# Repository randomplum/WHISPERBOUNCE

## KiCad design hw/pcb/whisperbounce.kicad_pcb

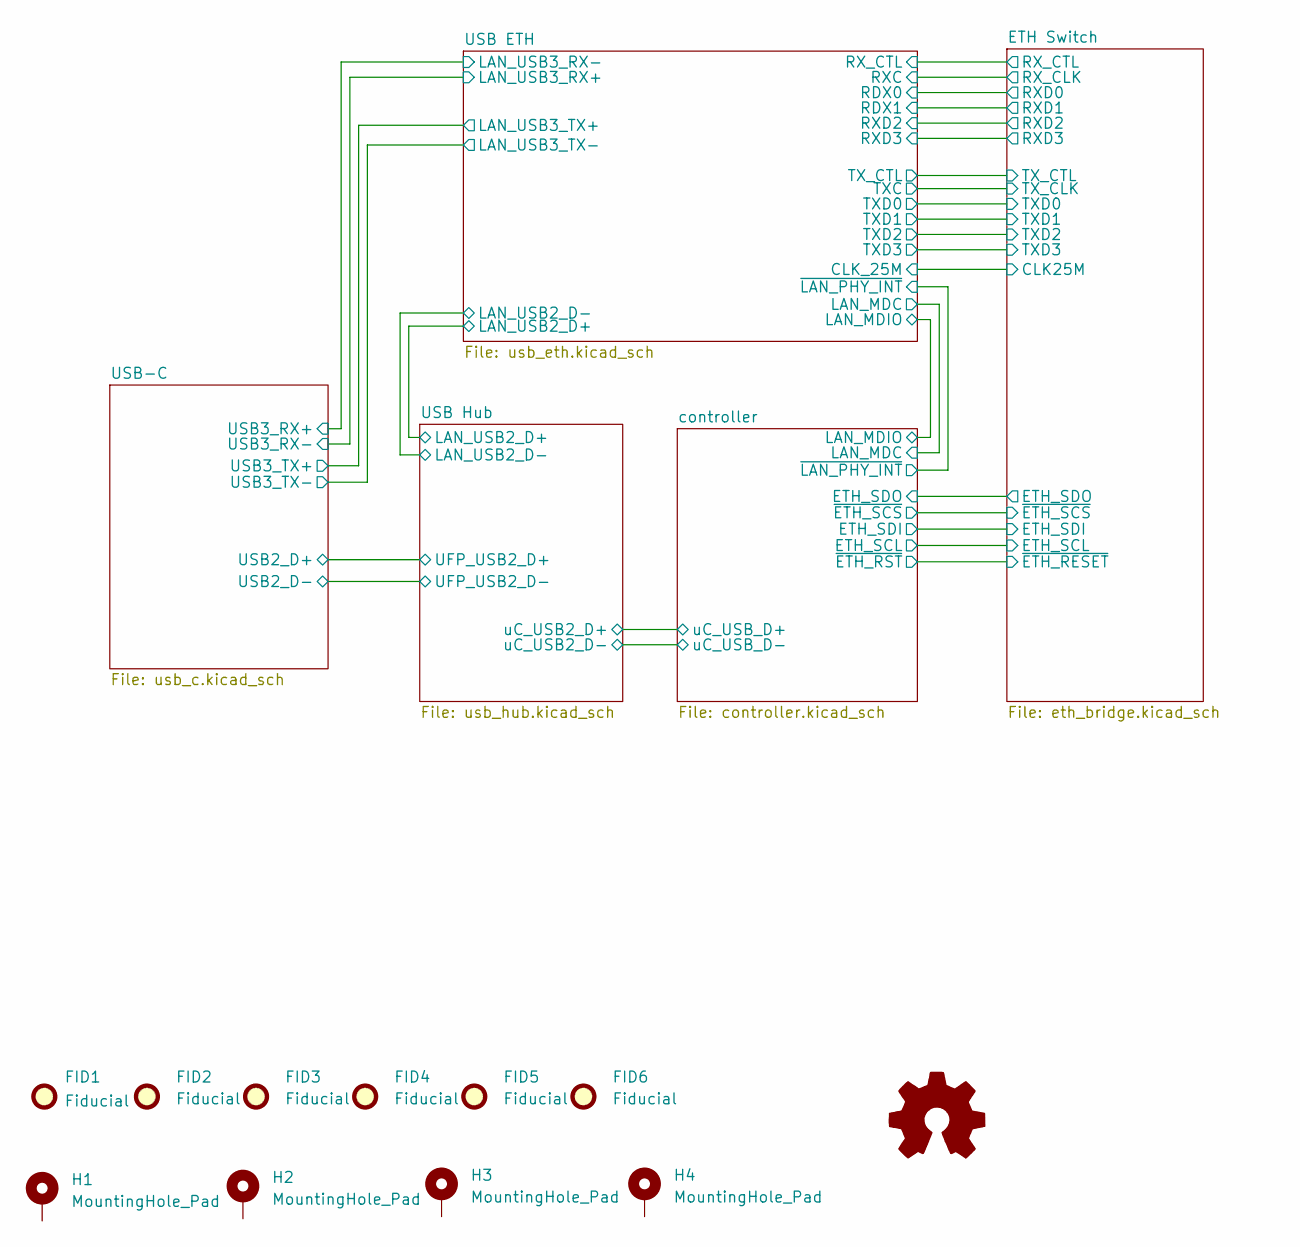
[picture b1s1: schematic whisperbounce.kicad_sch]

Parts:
FID1, FID2, FID3, FID4, FID5, FID6: Fiducial; Fiducial_0.75mm_Mask1.5mm
H1, H2, H3, H4: MountingHole_Pad; MountingHole_3.2mm_M3_Pad_Via

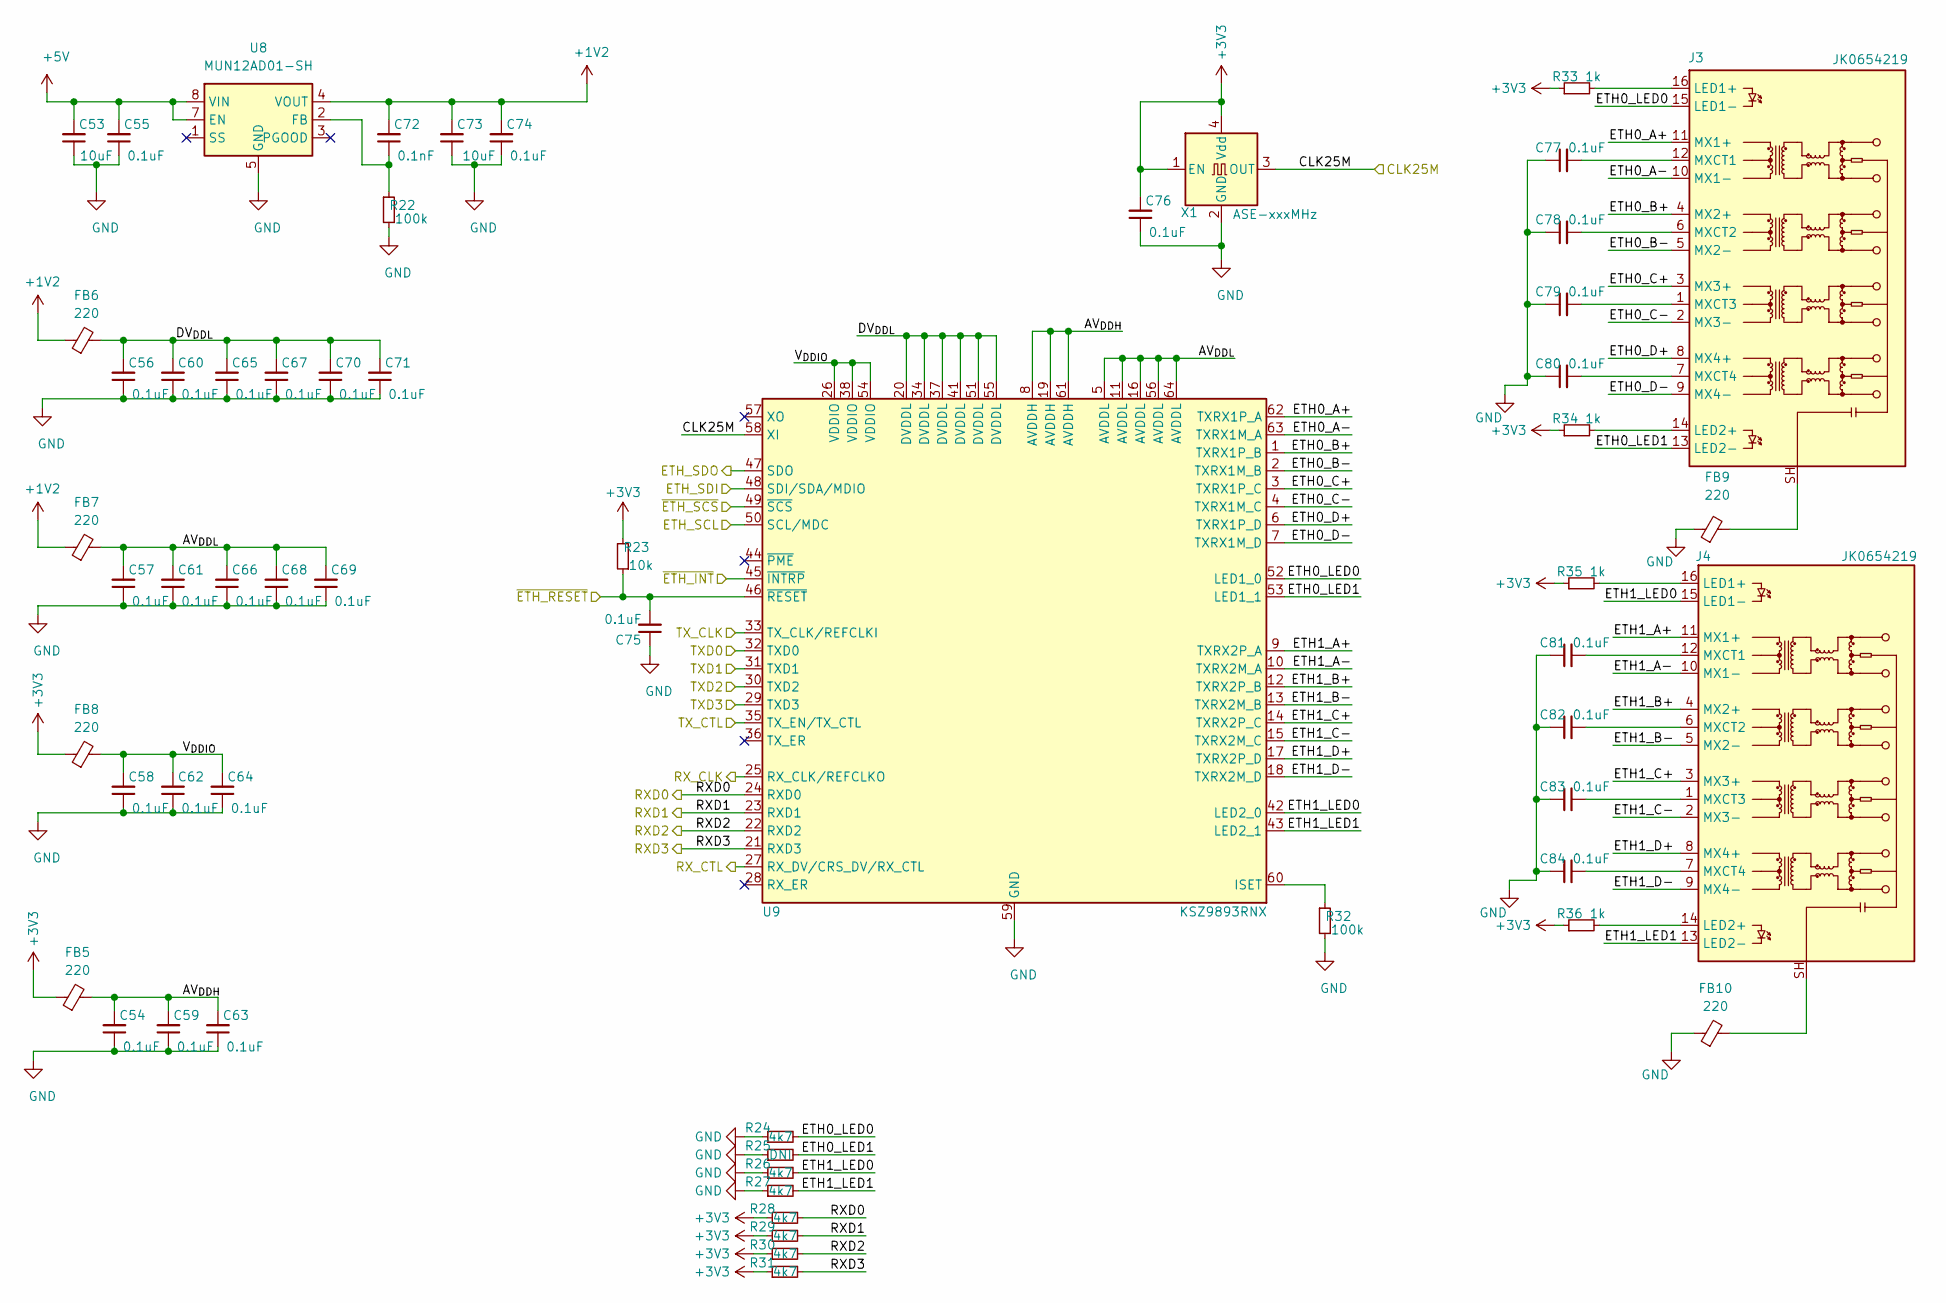
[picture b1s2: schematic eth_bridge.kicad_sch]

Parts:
C53, C73: 10uF; C_0402_1005Metric
C54, C55, C56, C57, C58, C59, C60, C61, C62, C63, C64, C65, C66, C67, C68, C69, C70, C71, C74, C75, C76, C77, C78, C79, C80, C81, C82, C83, C84: 0.1uF; C_0402_1005Metric
C72: 0.1nF; C_0402_1005Metric
FB5, FB6, FB7, FB8, FB9, FB10: 220; R_0603_1608Metric
J3, J4: JK0654219; RJ45_Pulse_JK0654219NL_Horizontal
R22, R32: 100k; R_0402_1005Metric
R23: 10k; R_0402_1005Metric
R24, R26, R27, R28, R29, R30, R31: 4k7; R_0402_1005Metric
R25: DNI; R_0402_1005Metric
R33, R34, R35, R36: 1k; R_0402_1005Metric
U8: MUN12AD01-SH; Converter_DCDC_Cyntec_MUN12AD01-SH
U9: KSZ9893RNX; QFN-64-1EP_8x8mm_P0.4mm_EP6.5x6.5mm_ThermalVias
X1: ASE-xxxMHz; Oscillator_SMD_Abracon_ASCO-4Pin_1.6x1.2mm

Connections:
+1V2: C72.2, C73.2, C74.2, FB6.1, FB7.1, U8.4 (VOUT)
+3V3: C76.2, FB5.1, FB8.1, R23.2, R28.1, R29.1, R30.1, R31.1, R33.1, R34.1, R35.1, R36.1, X1.1 (EN), X1.4 (Vdd); also elsewhere on the board
+5V: C53.2, C55.2, U8.7 (EN), U8.8 (VIN); also elsewhere on the board
/CLK_25M: U9.58 (XI), X1.3 (OUT); also elsewhere on the board
/ETH Switch/AV_{DDH}: C54.2, C59.2, C63.2, FB5.2, U9.8 (AVDDH), U9.19 (AVDDH), U9.61 (AVDDH)
/ETH Switch/AV_{DDL}: C57.2, C61.2, C66.2, C68.2, C69.2, FB7.2, U9.5 (AVDDL), U9.11 (AVDDL), U9.16 (AVDDL), U9.56 (AVDDL), U9.64 (AVDDL)
/ETH Switch/DV_{DDL}: C56.2, C60.2, C65.2, C67.2, C70.2, C71.2, FB6.2, U9.20 (DVDDL), U9.34 (DVDDL), U9.37 (DVDDL), U9.41 (DVDDL), U9.51 (DVDDL), U9.55 (DVDDL)
/ETH Switch/ETH0_A+: J3.11 (MX1+), U9.62 (TXRX1P_A)
/ETH Switch/ETH0_A-: J3.10 (MX1-), U9.63 (TXRX1M_A)
/ETH Switch/ETH0_B+: J3.4 (MX2+), U9.1 (TXRX1P_B)
/ETH Switch/ETH0_B-: J3.5 (MX2-), U9.2 (TXRX1M_B)
/ETH Switch/ETH0_C+: J3.3 (MX3+), U9.3 (TXRX1P_C)
/ETH Switch/ETH0_C-: J3.2 (MX3-), U9.4 (TXRX1M_C)
/ETH Switch/ETH0_D+: J3.8 (MX4+), U9.6 (TXRX1P_D)
/ETH Switch/ETH0_D-: J3.9 (MX4-), U9.7 (TXRX1M_D)
/ETH Switch/ETH0_LED0: J3.15 (LED1-), R24.2, U9.52 (LED1_0)
/ETH Switch/ETH0_LED1: J3.13 (LED2-), R25.2, U9.53 (LED1_1)
/ETH Switch/ETH1_A+: J4.11 (MX1+), U9.9 (TXRX2P_A)
/ETH Switch/ETH1_A-: J4.10 (MX1-), U9.10 (TXRX2M_A)
/ETH Switch/ETH1_B+: J4.4 (MX2+), U9.12 (TXRX2P_B)
/ETH Switch/ETH1_B-: J4.5 (MX2-), U9.13 (TXRX2M_B)
/ETH Switch/ETH1_C+: J4.3 (MX3+), U9.14 (TXRX2P_C)
/ETH Switch/ETH1_C-: J4.2 (MX3-), U9.15 (TXRX2M_C)
/ETH Switch/ETH1_D+: J4.8 (MX4+), U9.17 (TXRX2P_D)
/ETH Switch/ETH1_D-: J4.9 (MX4-), U9.18 (TXRX2M_D)
/ETH Switch/ETH1_LED0: J4.15 (LED1-), R26.2, U9.42 (LED2_0)
/ETH Switch/ETH1_LED1: J4.13 (LED2-), R27.2, U9.43 (LED2_1)
/ETH Switch/V_{DDIO}: C58.2, C62.2, C64.2, FB8.2, U9.26 (VDDIO), U9.38 (VDDIO), U9.54 (VDDIO)
/ETH_SCL: U9.50 (SCL/MDC); also elsewhere on the board
/ETH_SDI: U9.48 (SDI/SDA/MDIO); also elsewhere on the board
/ETH_SDO: U9.47 (SDO); also elsewhere on the board
/RXD0: R28.2, U9.24 (RXD0); also elsewhere on the board
/RXD1: R29.2, U9.23 (RXD1); also elsewhere on the board
/RXD2: R30.2, U9.22 (RXD2); also elsewhere on the board
/RXD3: R31.2, U9.21 (RXD3); also elsewhere on the board
/RX_CLK: U9.25 (RX_CLK/REFCLKO); also elsewhere on the board
/RX_CTL: U9.27 (RX_DV/CRS_DV/RX_CTL); also elsewhere on the board
/TXC: U9.33 (TX_CLK/REFCLKI); also elsewhere on the board
/TXD0: U9.32 (TXD0); also elsewhere on the board
/TXD1: U9.31 (TXD1); also elsewhere on the board
/TXD2: U9.30 (TXD2); also elsewhere on the board
/TXD3: U9.29 (TXD3); also elsewhere on the board
/TX_CTL: U9.35 (TX_EN/TX_CTL); also elsewhere on the board
/~ETH_RST: C75.2, R23.1, U9.46 (~RESET); also elsewhere on the board
/~ETH_SCS: U9.49 (~SCS); also elsewhere on the board
GND: C53.1, C54.1, C55.1, C56.1, C57.1, C58.1, C59.1, C60.1, C61.1, C62.1, C63.1, C64.1, C65.1, C66.1, C67.1, C68.1, C69.1, C70.1, C71.1, C73.1, C74.1, C75.1, C76.1, C77.1, C78.1, C79.1, C80.1, C81.1, C82.1, C83.1, C84.1, FB9.1, FB10.1, R22.2, R24.1, R25.1, R26.1, R27.1, R32.2, U8.5 (GND), U8.9 (GND), U9.59 (GND), U9.65 (GND), X1.2 (GND); also elsewhere on the board
unnamed: C72.1, R22.1, U8.2 (FB)
unnamed: C77.2, J3.12 (MXCT1)
unnamed: C78.2, J3.6 (MXCT2)
unnamed: C79.2, J3.1 (MXCT3)
unnamed: C80.2, J3.7 (MXCT4)
unnamed: C81.2, J4.12 (MXCT1)
unnamed: C82.2, J4.6 (MXCT2)
unnamed: C83.2, J4.1 (MXCT3)
unnamed: C84.2, J4.7 (MXCT4)
unnamed: FB9.2, J3.SH
unnamed: FB10.2, J4.SH
unnamed: J3.14 (LED2+), R34.2
unnamed: J3.16 (LED1+), R33.2
unnamed: J4.14 (LED2+), R36.2
unnamed: J4.16 (LED1+), R35.2
unnamed: R32.1, U9.60 (ISET)

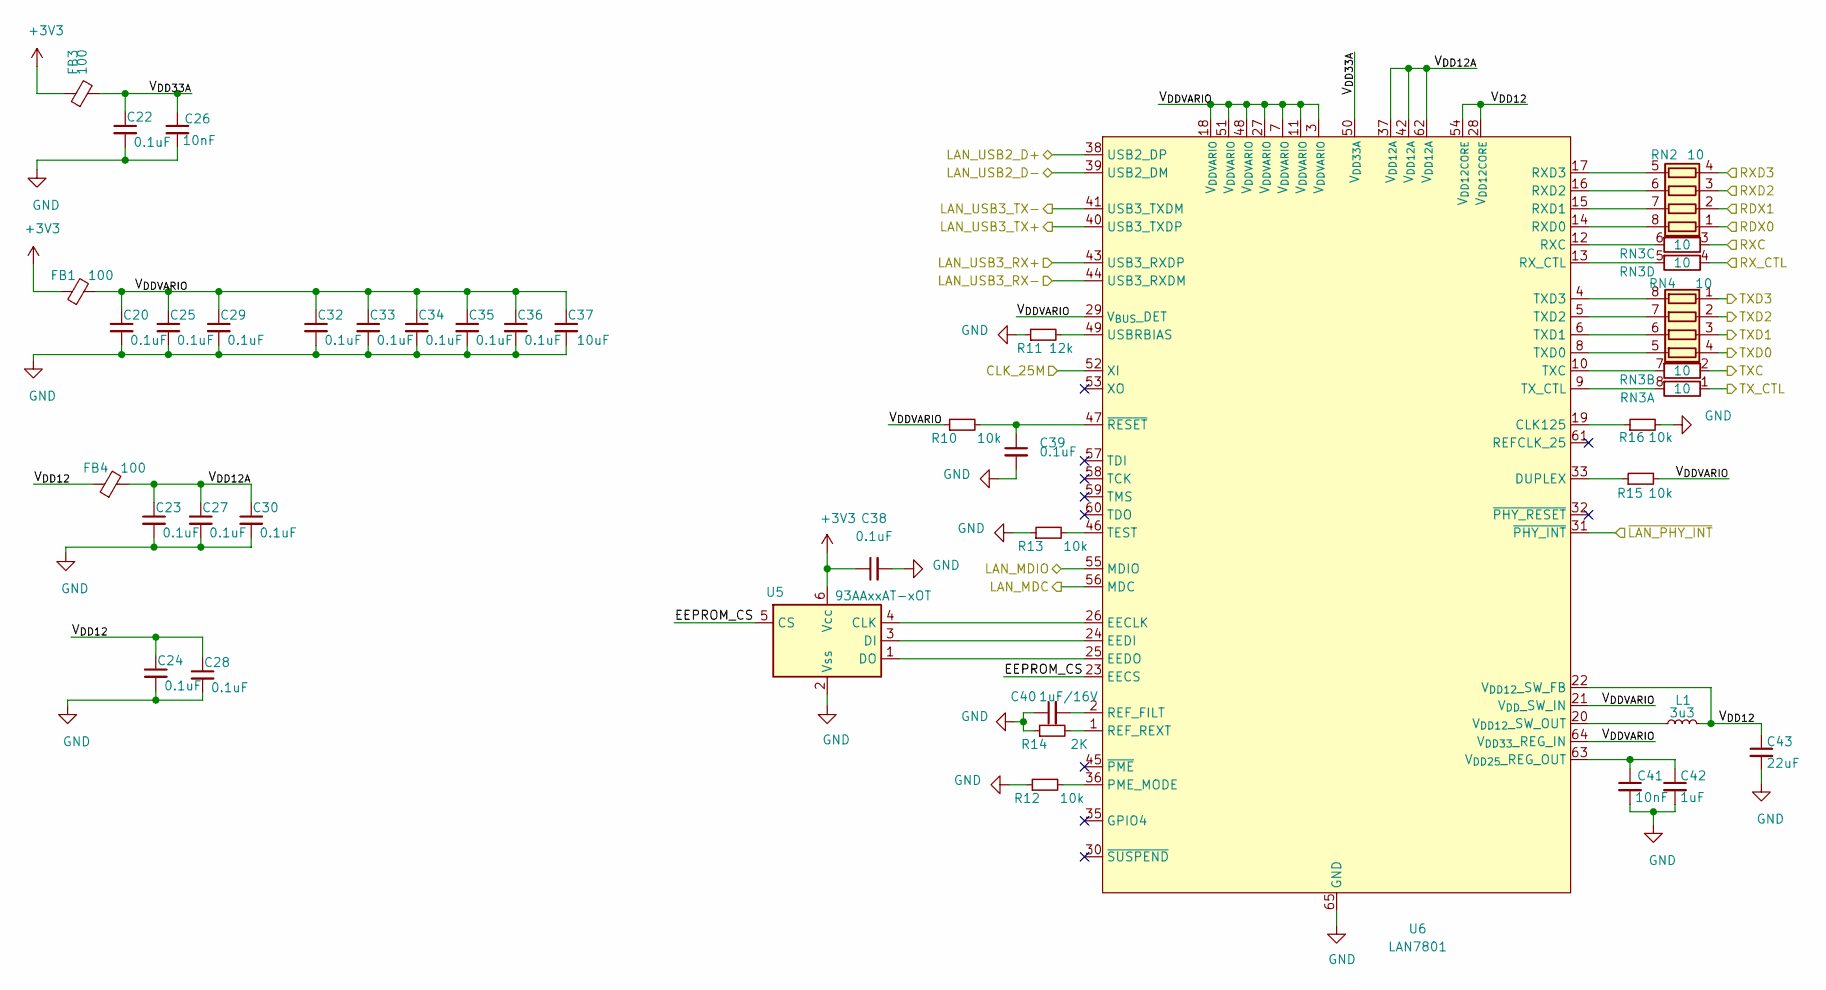
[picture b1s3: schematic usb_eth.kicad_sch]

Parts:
C20, C22, C23, C24, C25, C27, C28, C29, C30, C32, C33, C34, C35, C36, C38, C39: 0.1uF; C_0402_1005Metric
C26, C41: 10nF; C_0402_1005Metric
C37: 10uF; C_0402_1005Metric
C40: 1uF/16V; C_0402_1005Metric
C42: 1uF; C_0402_1005Metric
C43: 22uF; C_0805_2012Metric
FB1, FB3, FB4: 100; R_0603_1608Metric
L1: 3u3; L_Taiyo-Yuden_MD-2020
R10, R12, R13, R15, R16: 10k; R_0402_1005Metric
R11: 12k; R_0402_1005Metric
R14: 2K; R_0402_1005Metric
RN2, RN3, RN4: 10; R_Array_Convex_4x0402
U5: 93AAxxAT-xOT; SOT-23-6
U6: LAN7801; QFN-64-1EP_9x9mm_P0.5mm_EP6x6mm_ThermalVias

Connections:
+3V3: C38.1, FB1.1, FB3.1, U5.6 (Vсс); also elsewhere on the board
/CLK_25M: U6.52 (XI); also elsewhere on the board
/LAN_MDC: U6.56 (MDC); also elsewhere on the board
/LAN_MDIO: U6.55 (MDIO); also elsewhere on the board
/LAN_USB2_D+: U6.38 (USB2_DP); also elsewhere on the board
/LAN_USB2_D-: U6.39 (USB2_DM); also elsewhere on the board
/RXD0: RN2.1 (R1.1); also elsewhere on the board
/RXD1: RN2.2 (R2.1); also elsewhere on the board
/RXD2: RN2.3 (R3.1); also elsewhere on the board
/RXD3: RN2.4 (R4.1); also elsewhere on the board
/RX_CLK: RN3.3 (R3.1); also elsewhere on the board
/RX_CTL: RN3.4 (R4.1); also elsewhere on the board
/TXC: RN3.2 (R2.1); also elsewhere on the board
/TXD0: RN4.4 (R4.1); also elsewhere on the board
/TXD1: RN4.3 (R3.1); also elsewhere on the board
/TXD2: RN4.2 (R2.1); also elsewhere on the board
/TXD3: RN4.1 (R1.1); also elsewhere on the board
/TX_CTL: RN3.1 (R1.1); also elsewhere on the board
/USB3_RX+: U6.44 (USB3_RXDM); also elsewhere on the board
/USB3_RX-: U6.43 (USB3_RXDP); also elsewhere on the board
/USB3_TX+: U6.40 (USB3_TXDP); also elsewhere on the board
/USB3_TX-: U6.41 (USB3_TXDM); also elsewhere on the board
/USB ETH/EEPROM_CS: U5.5 (CS), U6.23 (EECS)
/USB ETH/V_{DD12A}: C23.1, C27.1, C30.1, FB4.2, U6.37 (V_{DD12A}), U6.42 (V_{DD12A}), U6.62 (V_{DD12A})
/USB ETH/V_{DD12}: C24.1, C28.1, C43.1, FB4.1, L1.2, U6.22 (V_{DD12}_SW_FB), U6.28 (V_{DD12CORE}), U6.54 (V_{DD12CORE})
/USB ETH/V_{DD33A}: C22.1, C26.1, FB3.2, U6.50 (V_{DD33A})
/USB ETH/V_{DDVARIO}: C20.1, C25.1, C29.1, C32.1, C33.1, C34.1, C35.1, C36.1, C37.1, FB1.2, R10.1, R15.2, U6.3 (V_{DDVARIO}), U6.7 (V_{DDVARIO}), U6.11 (V_{DDVARIO}), U6.18 (V_{DDVARIO}), U6.21 (V_{DD}_SW_IN), U6.27 (V_{DDVARIO}), U6.29 (V_{BUS}_DET), U6.48 (V_{DDVARIO}), U6.51 (V_{DDVARIO}), U6.64 (V_{DD33}_REG_IN)
/~LAN_PHY_INT: U6.31 (~PHY_INT); also elsewhere on the board
GND: C20.2, C22.2, C23.2, C24.2, C25.2, C26.2, C27.2, C28.2, C29.2, C30.2, C32.2, C33.2, C34.2, C35.2, C36.2, C37.2, C38.2, C39.2, C40.1, C41.2, C42.2, C43.2, R11.1, R12.1, R13.1, R14.1, R16.2, U5.2 (Vss), U6.65 (GND); also elsewhere on the board
unnamed: C39.1, R10.2, U6.47 (~RESET)
unnamed: C40.2, U6.2 (REF_FILT)
unnamed: C41.1, C42.1, U6.63 (V_{DD25}_REG_OUT)
unnamed: L1.1, U6.20 (V_{DD12}_SW_OUT)
unnamed: R11.2, U6.49 (USBRBIAS)
unnamed: R12.2, U6.36 (PME_MODE)
unnamed: R13.2, U6.46 (TEST)
unnamed: R14.2, U6.1 (REF_REXT)
unnamed: R15.1, U6.33 (DUPLEX)
unnamed: R16.1, U6.19 (CLK125)
unnamed: RN2.5 (R4.2), U6.17 (RXD3)
unnamed: RN2.6 (R3.2), U6.16 (RXD2)
unnamed: RN2.7 (R2.2), U6.15 (RXD1)
unnamed: RN2.8 (R1.2), U6.14 (RXD0)
unnamed: RN3.5 (R4.2), U6.13 (RX_CTL)
unnamed: RN3.6 (R3.2), U6.12 (RXC)
unnamed: RN3.7 (R2.2), U6.10 (TXC)
unnamed: RN3.8 (R1.2), U6.9 (TX_CTL)
unnamed: RN4.5 (R4.2), U6.8 (TXD0)
unnamed: RN4.6 (R3.2), U6.6 (TXD1)
unnamed: RN4.7 (R2.2), U6.5 (TXD2)
unnamed: RN4.8 (R1.2), U6.4 (TXD3)
unnamed: U5.1 (DO), U6.25 (EEDO)
unnamed: U5.3 (DI), U6.24 (EEDI)
unnamed: U5.4 (CLK), U6.26 (EECLK)

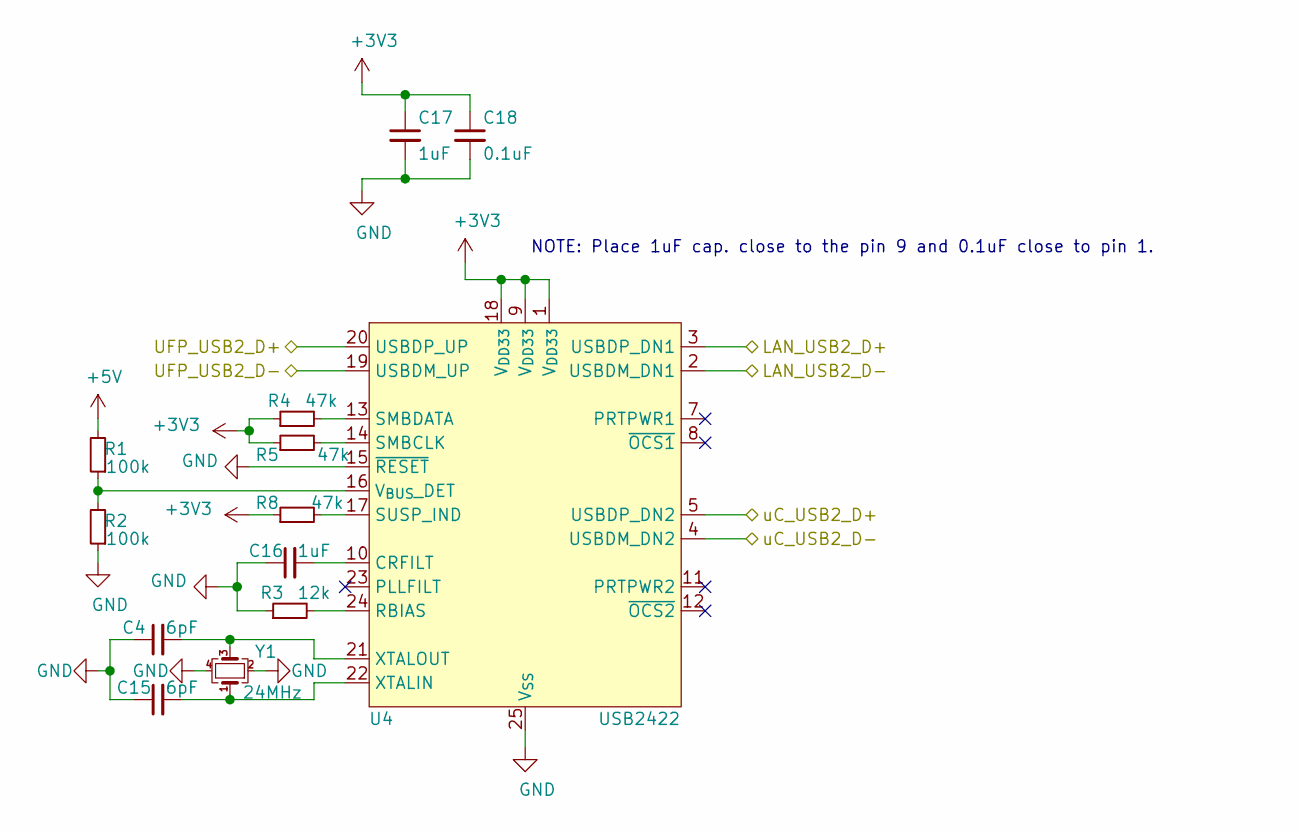
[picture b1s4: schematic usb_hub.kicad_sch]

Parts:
C4, C15: 6pF; C_0402_1005Metric
C16, C17: 1uF; C_0402_1005Metric
C18: 0.1uF; C_0402_1005Metric
R1, R2: 100k; R_0402_1005Metric
R3: 12k; R_0402_1005Metric
R4, R5, R8: 47k; R_0402_1005Metric
U4: USB2422; QFN-24-1EP_4x4mm_P0.5mm_EP2.6x2.6mm
Y1: 24MHz; Oscillator_SMD_Abracon_ASCO-4Pin_1.6x1.2mm

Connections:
+3V3: C17.1, C18.1, R4.1, R5.1, R8.1, U4.1 (V_{DD33}), U4.9 (V_{DD33}), U4.18 (V_{DD33}); also elsewhere on the board
+5V: R1.2; also elsewhere on the board
/LAN_USB2_D+: U4.3 (USBDP_DN1); also elsewhere on the board
/LAN_USB2_D-: U4.2 (USBDM_DN1); also elsewhere on the board
/UFP_USB2_D+: U4.20 (USBDP_UP); also elsewhere on the board
/UFP_USB2_D-: U4.19 (USBDM_UP); also elsewhere on the board
/uC_USB_D+: U4.5 (USBDP_DN2); also elsewhere on the board
/uC_USB_D-: U4.4 (USBDM_DN2); also elsewhere on the board
GND: C4.1, C15.1, C16.1, C17.2, C18.2, R2.1, R3.1, U4.15 (~RESET), U4.25 (V_{SS}), Y1.2, Y1.4; also elsewhere on the board
unnamed: C4.2, U4.21 (XTALOUT), Y1.3
unnamed: C15.2, U4.22 (XTALIN), Y1.1
unnamed: C16.2, U4.10 (CRFILT)
unnamed: R1.1, R2.2, U4.16 (V_{BUS}_DET)
unnamed: R3.2, U4.24 (RBIAS)
unnamed: R4.2, U4.13 (SMBDATA)
unnamed: R5.2, U4.14 (SMBCLK)
unnamed: R8.2, U4.17 (SUSP_IND)

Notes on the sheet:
NOTE: Place 1uF cap. close to the pin 9 and 0.1uF close to pin 1.

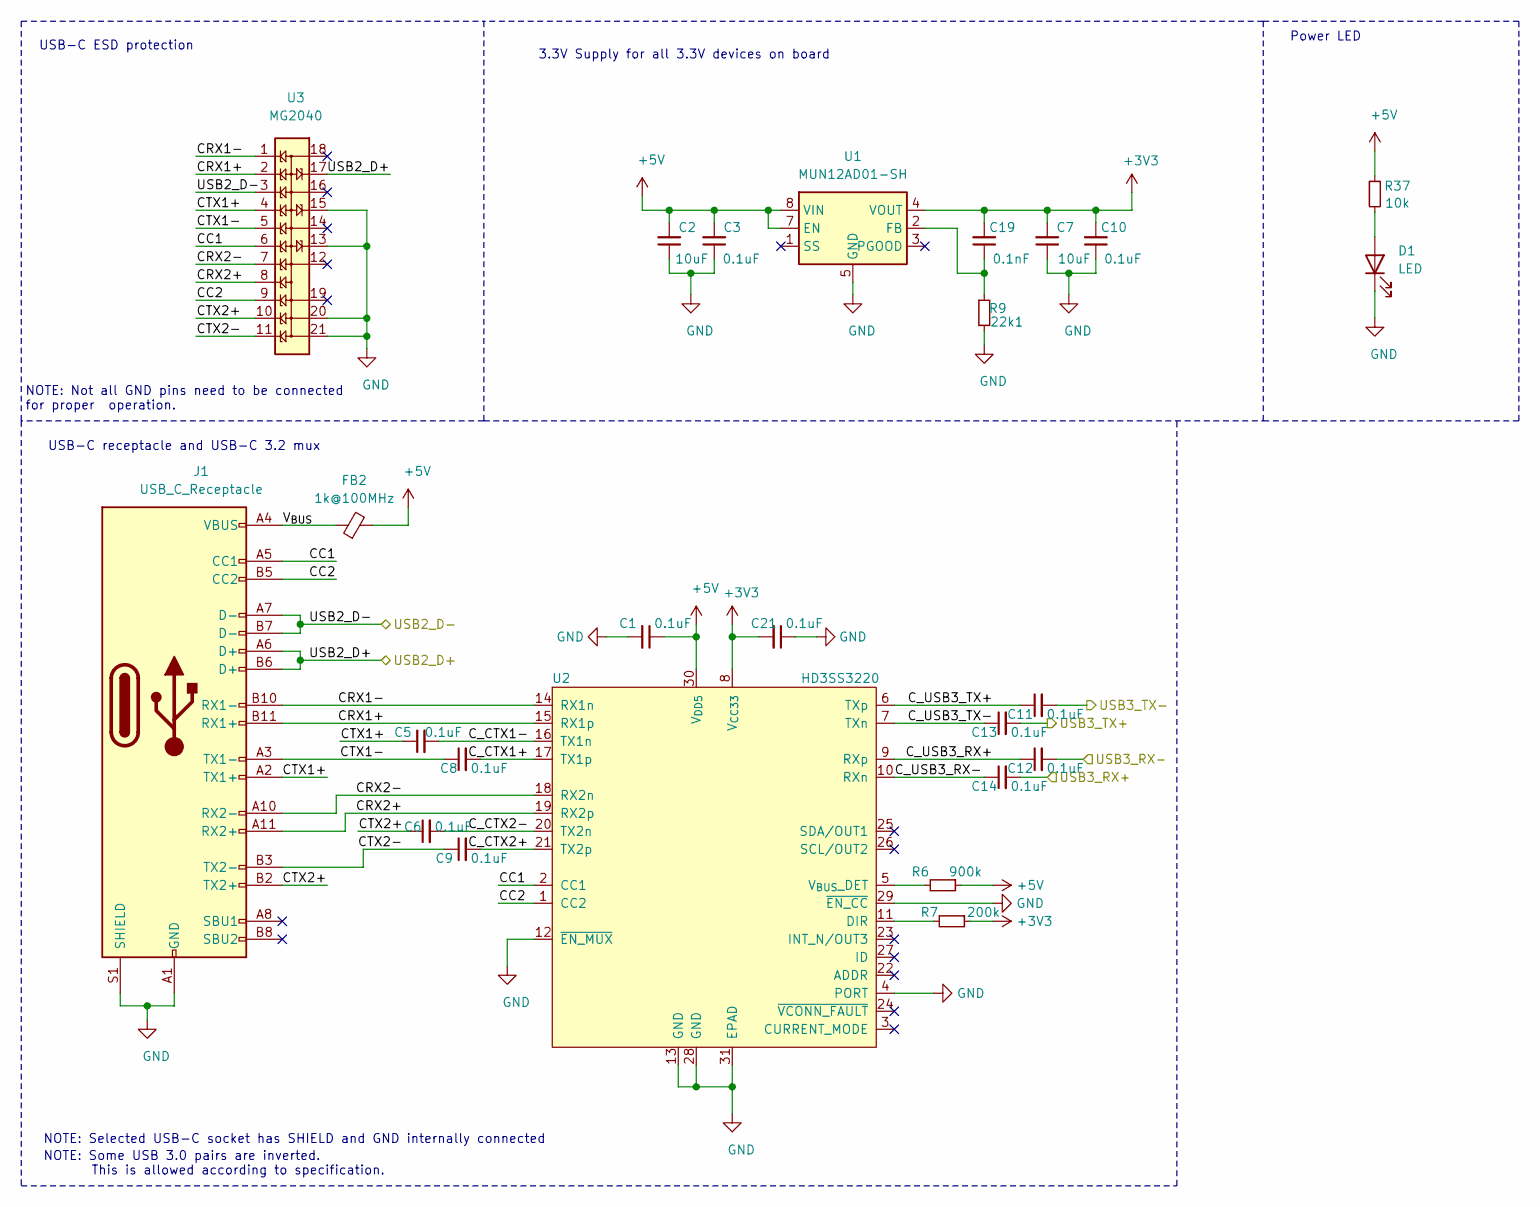
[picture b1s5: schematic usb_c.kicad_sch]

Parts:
C1, C3, C5, C6, C8, C9, C10, C11, C12, C13, C14, C21: 0.1uF; C_0402_1005Metric
C2, C7: 10uF; C_0402_1005Metric
C19: 0.1nF; C_0402_1005Metric
D1: LED; LED_0402_1005Metric
FB2: 1k@100MHz; R_0603_1608Metric
J1: USB_C_Receptacle; USB_C_Receptacle_Molex_1054500101
R6: 900k; R_0402_1005Metric
R7: 200k; R_0402_1005Metric
R9: 22k1; R_0402_1005Metric
R37: 10k; R_0402_1005Metric
U1: MUN12AD01-SH; Converter_DCDC_Cyntec_MUN12AD01-SH
U2: HD3SS3220; WQFP-30-1EP_4.6x2.6mm_P0.4mm_EP3.2x1.2mm
U3: MG2040; UDFN-18-3EP_5.5x1.5mm_P0.5mm_EP0.5x0.5mm

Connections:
+3V3: C7.2, C10.2, C19.2, C21.2, R7.1, U1.4 (VOUT), U2.8 (V_{CC33}); also elsewhere on the board
+5V: C1.1, C2.2, C3.2, FB2.2, R6.1, R37.1, U1.7 (EN), U1.8 (VIN), U2.30 (V_{DD5}); also elsewhere on the board
/UFP_USB2_D+: J1.A6 (D+), J1.B6 (D+), U3.17; also elsewhere on the board
/UFP_USB2_D-: J1.A7 (D-), J1.B7 (D-), U3.3; also elsewhere on the board
/USB3_RX+: C14.2; also elsewhere on the board
/USB3_RX-: C12.2; also elsewhere on the board
/USB3_TX+: C13.2; also elsewhere on the board
/USB3_TX-: C11.2; also elsewhere on the board
/USB-C/CC1: J1.A5 (CC1), U2.2 (CC1), U3.6
/USB-C/CC2: J1.B5 (CC2), U2.1 (CC2), U3.9
/USB-C/CRX1+: J1.B11 (RX1+), U2.15 (RX1p), U3.2
/USB-C/CRX1-: J1.B10 (RX1-), U2.14 (RX1n), U3.1
/USB-C/CRX2+: J1.A11 (RX2+), U2.19 (RX2p), U3.8
/USB-C/CRX2-: J1.A10 (RX2-), U2.18 (RX2n), U3.7
/USB-C/CTX1+: C5.1, J1.A2 (TX1+), U3.4
/USB-C/CTX1-: C8.1, J1.A3 (TX1-), U3.5
/USB-C/CTX2+: C6.1, J1.B2 (TX2+), U3.10
/USB-C/CTX2-: C9.1, J1.B3 (TX2-), U3.11
/USB-C/C_CTX1+: C8.2, U2.17 (TX1p)
/USB-C/C_CTX1-: C5.2, U2.16 (TX1n)
/USB-C/C_CTX2+: C9.2, U2.21 (TX2p)
/USB-C/C_CTX2-: C6.2, U2.20 (TX2n)
/USB-C/C_USB3_RX+: C12.1, U2.9 (RXp)
/USB-C/C_USB3_RX-: C14.1, U2.10 (RXn)
/USB-C/C_USB3_TX+: C11.1, U2.6 (TXp)
/USB-C/C_USB3_TX-: C13.1, U2.7 (TXn)
/USB-C/V_{BUS}: FB2.1, J1.A4 (VBUS), J1.A9 (VBUS), J1.B4 (VBUS), J1.B9 (VBUS)
GND: C1.2, C2.1, C3.1, C7.1, C10.1, C21.1, D1.1 (K), J1.A1 (GND), J1.A12 (GND), J1.B1 (GND), J1.B12 (GND), J1.S1 (SHIELD), R9.2, U1.5 (GND), U1.9 (GND), U2.4 (PORT), U2.12 (~EN_MUX), U2.13 (GND), U2.28 (GND), U2.29 (~EN_CC), U2.31 (EPAD), U3.13, U3.15, U3.20, U3.21; also elsewhere on the board
unnamed: C19.1, R9.1, U1.2 (FB)
unnamed: D1.2 (A), R37.2
unnamed: R6.2, U2.5 (V_{BUS}_DET)
unnamed: R7.2, U2.11 (DIR)

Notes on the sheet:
NOTE: Not all GND pins need to be connected for proper operation.
USB-C ESD protection
NOTE: Selected USB-C socket has SHIELD and GND internally connected
NOTE: Some USB 3.0 pairs are inverted. This is allowed according to specification.
USB-C receptacle and USB-C 3.2 mux
3.3V Supply for all 3.3V devices on board
Power LED

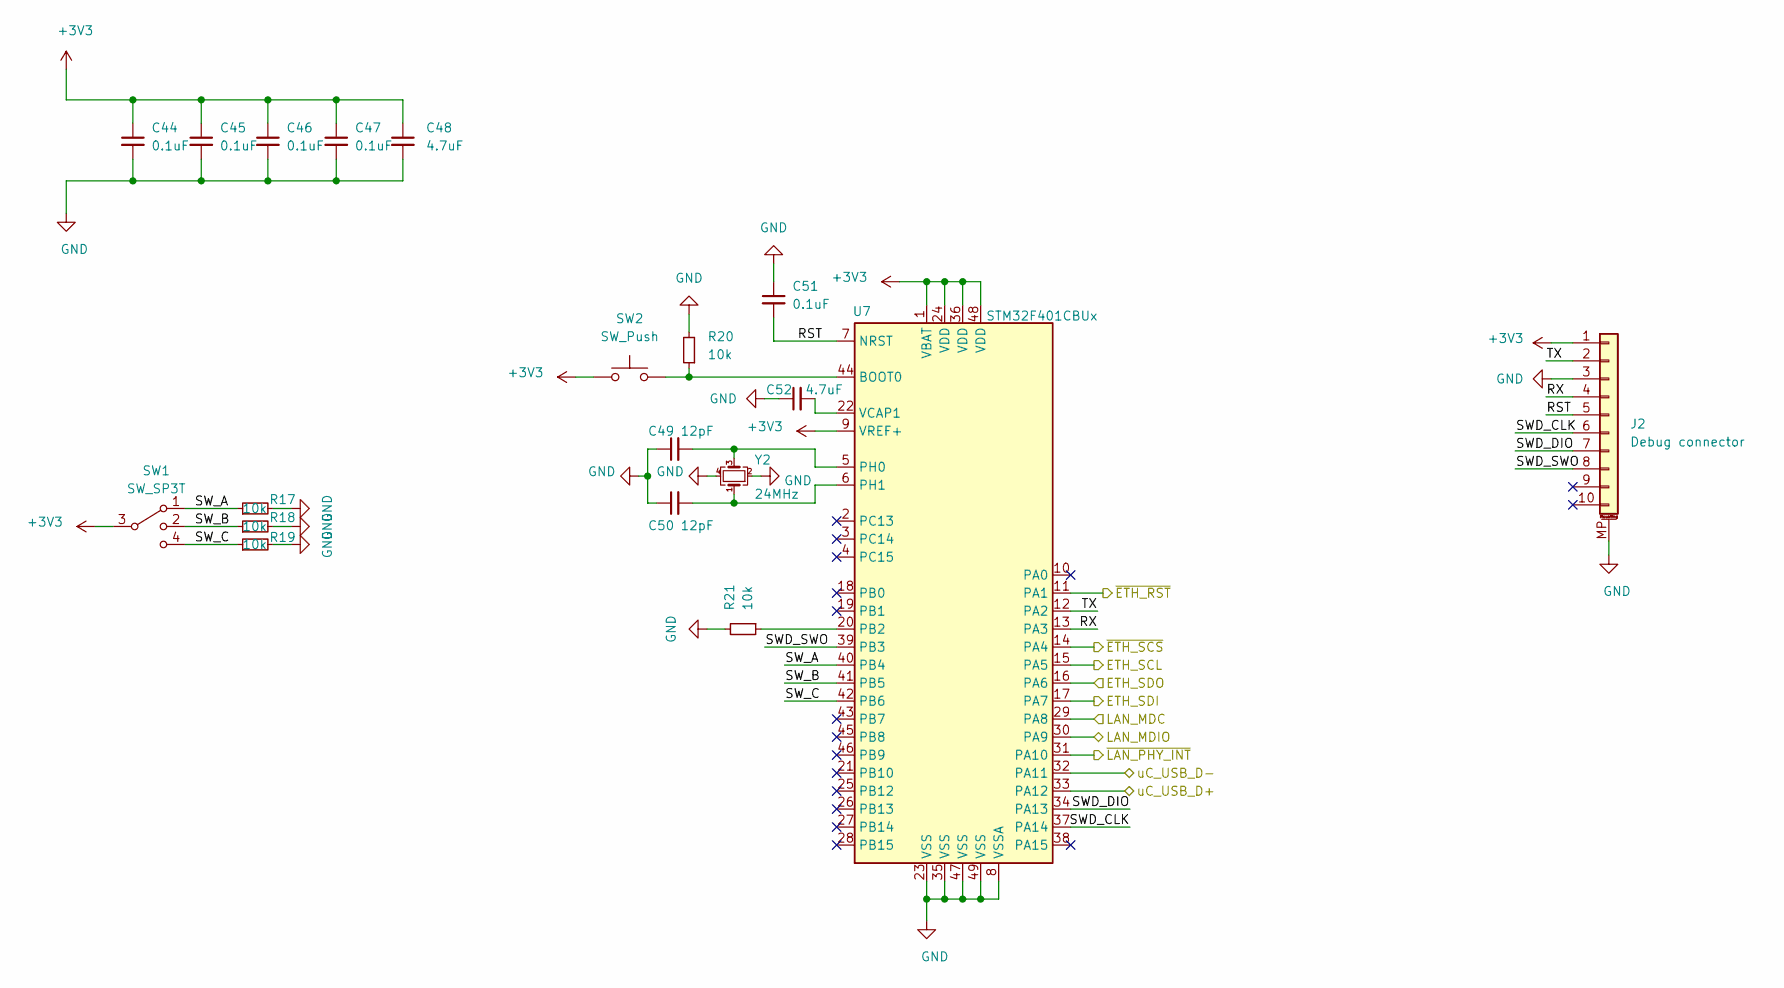
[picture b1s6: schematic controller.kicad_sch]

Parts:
C44, C45, C46, C47, C51: 0.1uF; C_0402_1005Metric
C48, C52: 4.7uF; C_0402_1005Metric
C49, C50: 12pF; C_0402_1005Metric
J2: Debug connector; Hirose_FH12-10S-0.5SH_1x10-1MP_P0.50mm_Horizontal
R17, R18, R19, R20, R21: 10k; R_0402_1005Metric
SW1: SW_SP3T; SW_SP3T_PCM13
SW2: SW_Push; SW_SPST_B3U-3000P
U7: STM32F401CBUx; QFN-48-1EP_7x7mm_P0.5mm_EP5.6x5.6mm
Y2: 24MHz; Oscillator_SMD_Abracon_ASCO-4Pin_1.6x1.2mm

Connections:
+3V3: C44.1, C45.1, C46.1, C47.1, C48.1, J2.1, SW1.3, SW2.1, U7.1 (VBAT), U7.9 (VREF+), U7.24 (VDD), U7.36 (VDD), U7.48 (VDD); also elsewhere on the board
/ETH_SCL: U7.15 (PA5); also elsewhere on the board
/ETH_SDI: U7.17 (PA7); also elsewhere on the board
/ETH_SDO: U7.16 (PA6); also elsewhere on the board
/LAN_MDC: U7.29 (PA8); also elsewhere on the board
/LAN_MDIO: U7.30 (PA9); also elsewhere on the board
/controller/RST: C51.2, J2.5, U7.7 (NRST)
/controller/RX: J2.4, U7.13 (PA3)
/controller/SWD_CLK: J2.6, U7.37 (PA14)
/controller/SWD_DIO: J2.7, U7.34 (PA13)
/controller/SWD_SWO: J2.8, U7.39 (PB3)
/controller/SW_A: R17.1, SW1.1, U7.40 (PB4)
/controller/SW_B: R18.1, SW1.2, U7.41 (PB5)
/controller/SW_C: R19.1, SW1.4, U7.42 (PB6)
/controller/TX: J2.2, U7.12 (PA2)
/uC_USB_D+: U7.33 (PA12); also elsewhere on the board
/uC_USB_D-: U7.32 (PA11); also elsewhere on the board
/~ETH_RST: U7.11 (PA1); also elsewhere on the board
/~ETH_SCS: U7.14 (PA4); also elsewhere on the board
/~LAN_PHY_INT: U7.31 (PA10); also elsewhere on the board
GND: C44.2, C45.2, C46.2, C47.2, C48.2, C49.1, C50.1, C51.1, C52.1, J2.3, J2.MP (MountPin), R17.2, R18.2, R19.2, R20.2, R21.2, U7.8 (VSSA), U7.23 (VSS), U7.35 (VSS), U7.47 (VSS), U7.49 (VSS), Y2.2, Y2.4; also elsewhere on the board
unnamed: C49.2, U7.5 (PH0), Y2.3
unnamed: C50.2, U7.6 (PH1), Y2.1
unnamed: C52.2, U7.22 (VCAP1)
unnamed: R20.1, SW2.2, U7.44 (BOOT0)
unnamed: R21.1, U7.20 (PB2)

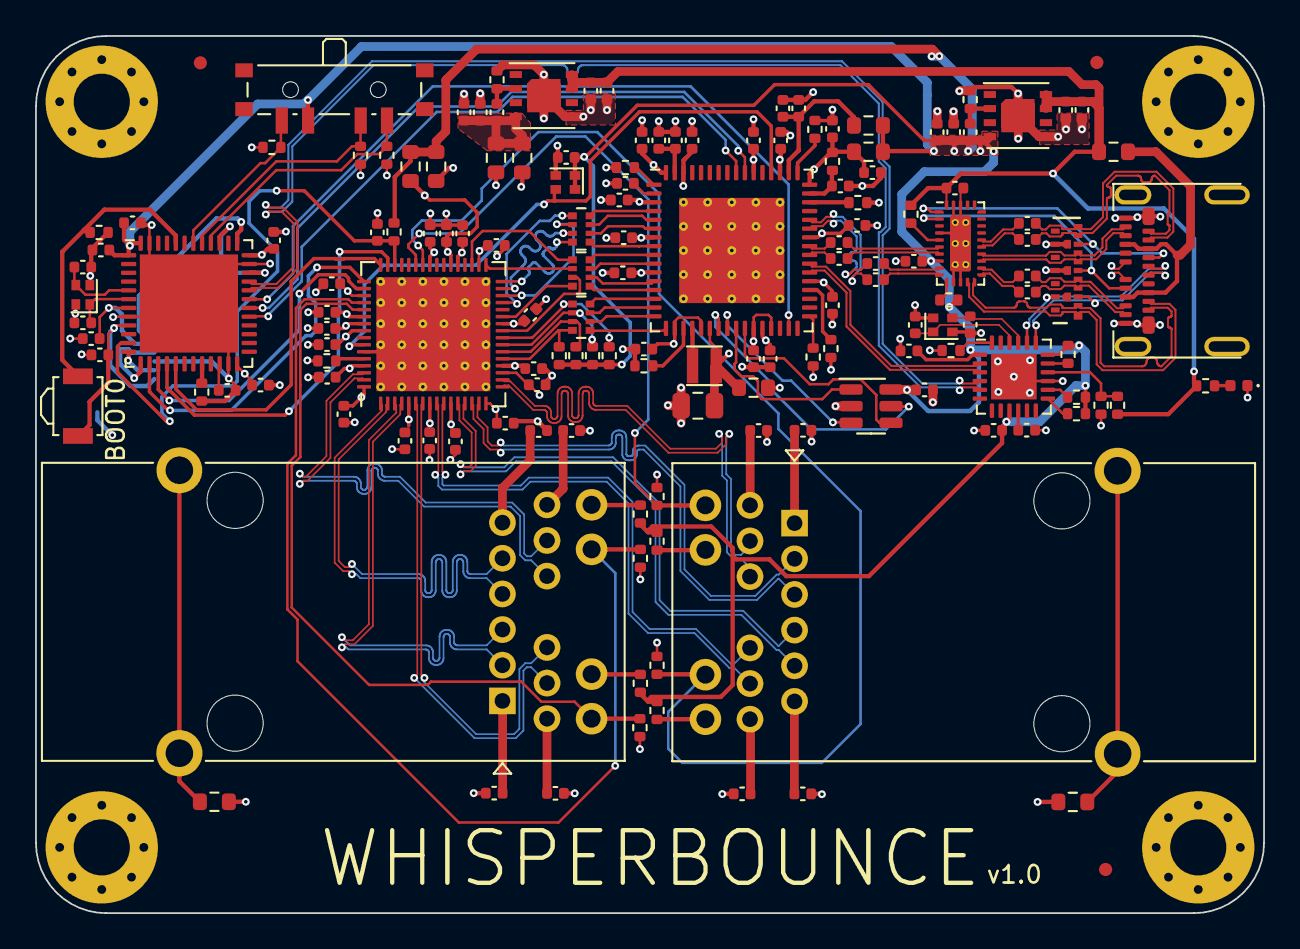
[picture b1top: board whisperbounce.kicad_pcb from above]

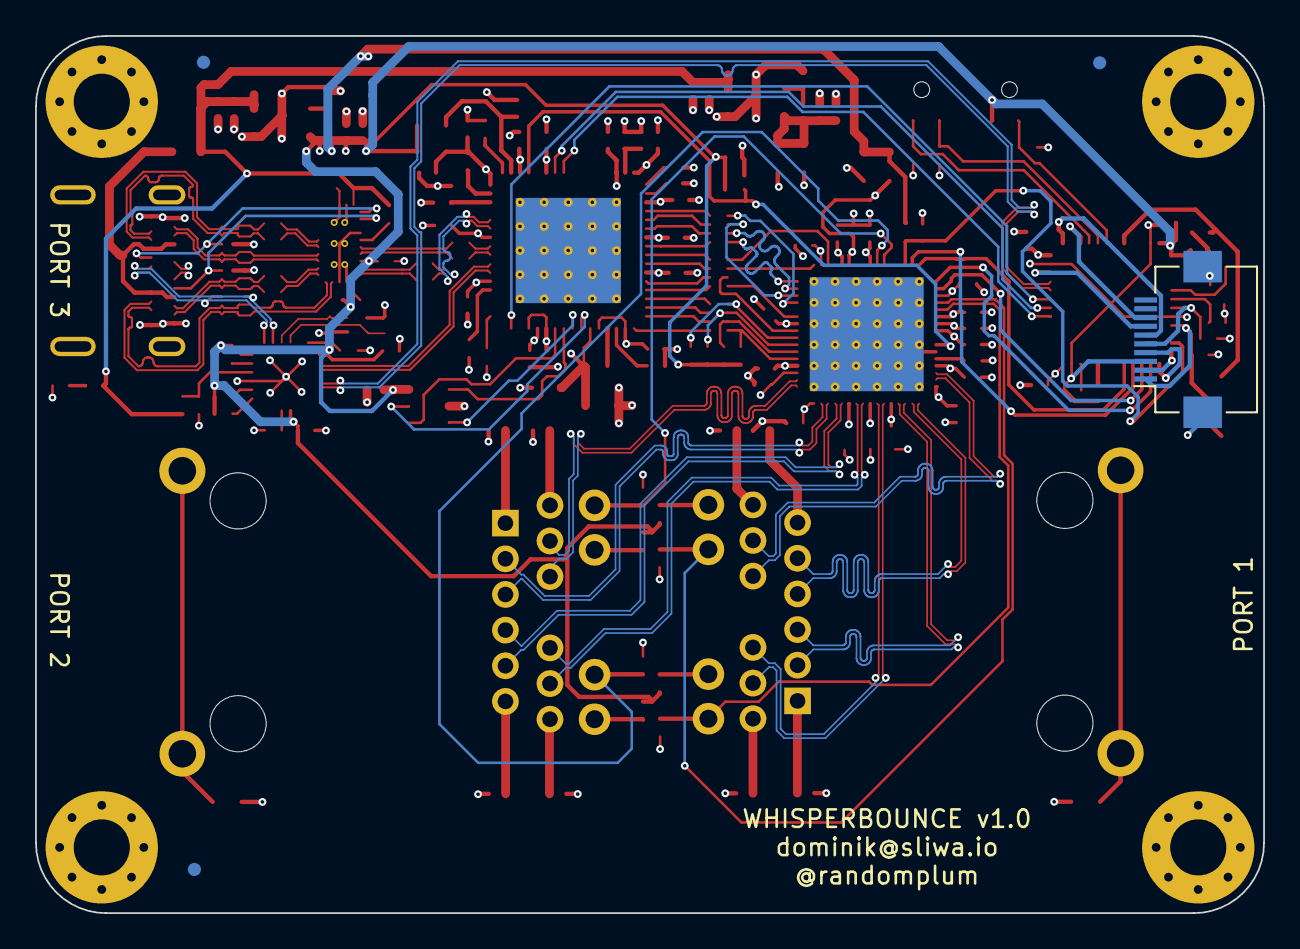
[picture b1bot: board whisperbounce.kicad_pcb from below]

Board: 4 copper layers, 70.0 x 50.0 mm, 163 parts (4 on the bottom side), 150 nets.

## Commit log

2020-11-27 whisperbouce: initial commit
2020-11-27 whisperbounce: Schematics
2020-11-28 whisperbounce: assign footprints
2020-11-29 whisperbounce: pcb v1
    Includes schematic and assigment tweaks
2020-11-30 WHISPERBOUNCE: v1.0 production data
2020-11-30 whisperbounce: fix models and generate v1.0 STEP
2020-12-20 sw: add STM32CubeF4 submodule
2020-12-20 sw: Initial sw
    Builds with cmake, includes clock configuration and uart/printf
2021-01-31 CMakeList.txt: improve cmake cross-platform compatiblity
